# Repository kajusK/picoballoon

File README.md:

Picoballoon challange 2019, team deadbadger probe
-------------------------------------------------

This repo contains source codes and hw design of the picoballoon probe designed
for https://www.hvezdarna.cz/?p=7694.

Due to the lack of free time, the pcb is very suboptimal as I needed single sided
board with wider traces for diy manufacturing process (made it few days before the
launch, didn't have enough time to send it to a pcb house).

The circuit contains:
- MCU stm32f070
- GPS u-blox max-m8
- Lora module HPD13
- Analog thermometer
- Digital pressure sensor MS5607 (failed to make it working before start - getting nack all the time)
- Solar panel that charges the supercap (wanted bare cells from china, but delivery time was too long, used one quite heavy panel from my junk box)
- 3.3 V boost switching power supply with startup circuit (starts around 2,5 V)

The software is quite simplified too. The Lmic library takes care of the LoRa
communications. Minmea handles processing nmea messages from gps. For future
reference, the libopencm3 is not the best option when dealing with stm32f0
family, I've had serious issues with rtc wakeup timer and failed
to wake up from deep sleep on rtc events anyway...

The code does following:
- Initialize peripherals
- Send LoRa join request
- Try to get the gps position
- After gps fix or timeout, send data over the LoRa connection and shutdown

Sending period depends on amount of sunlight (solar cell current) and supercap
capacity.

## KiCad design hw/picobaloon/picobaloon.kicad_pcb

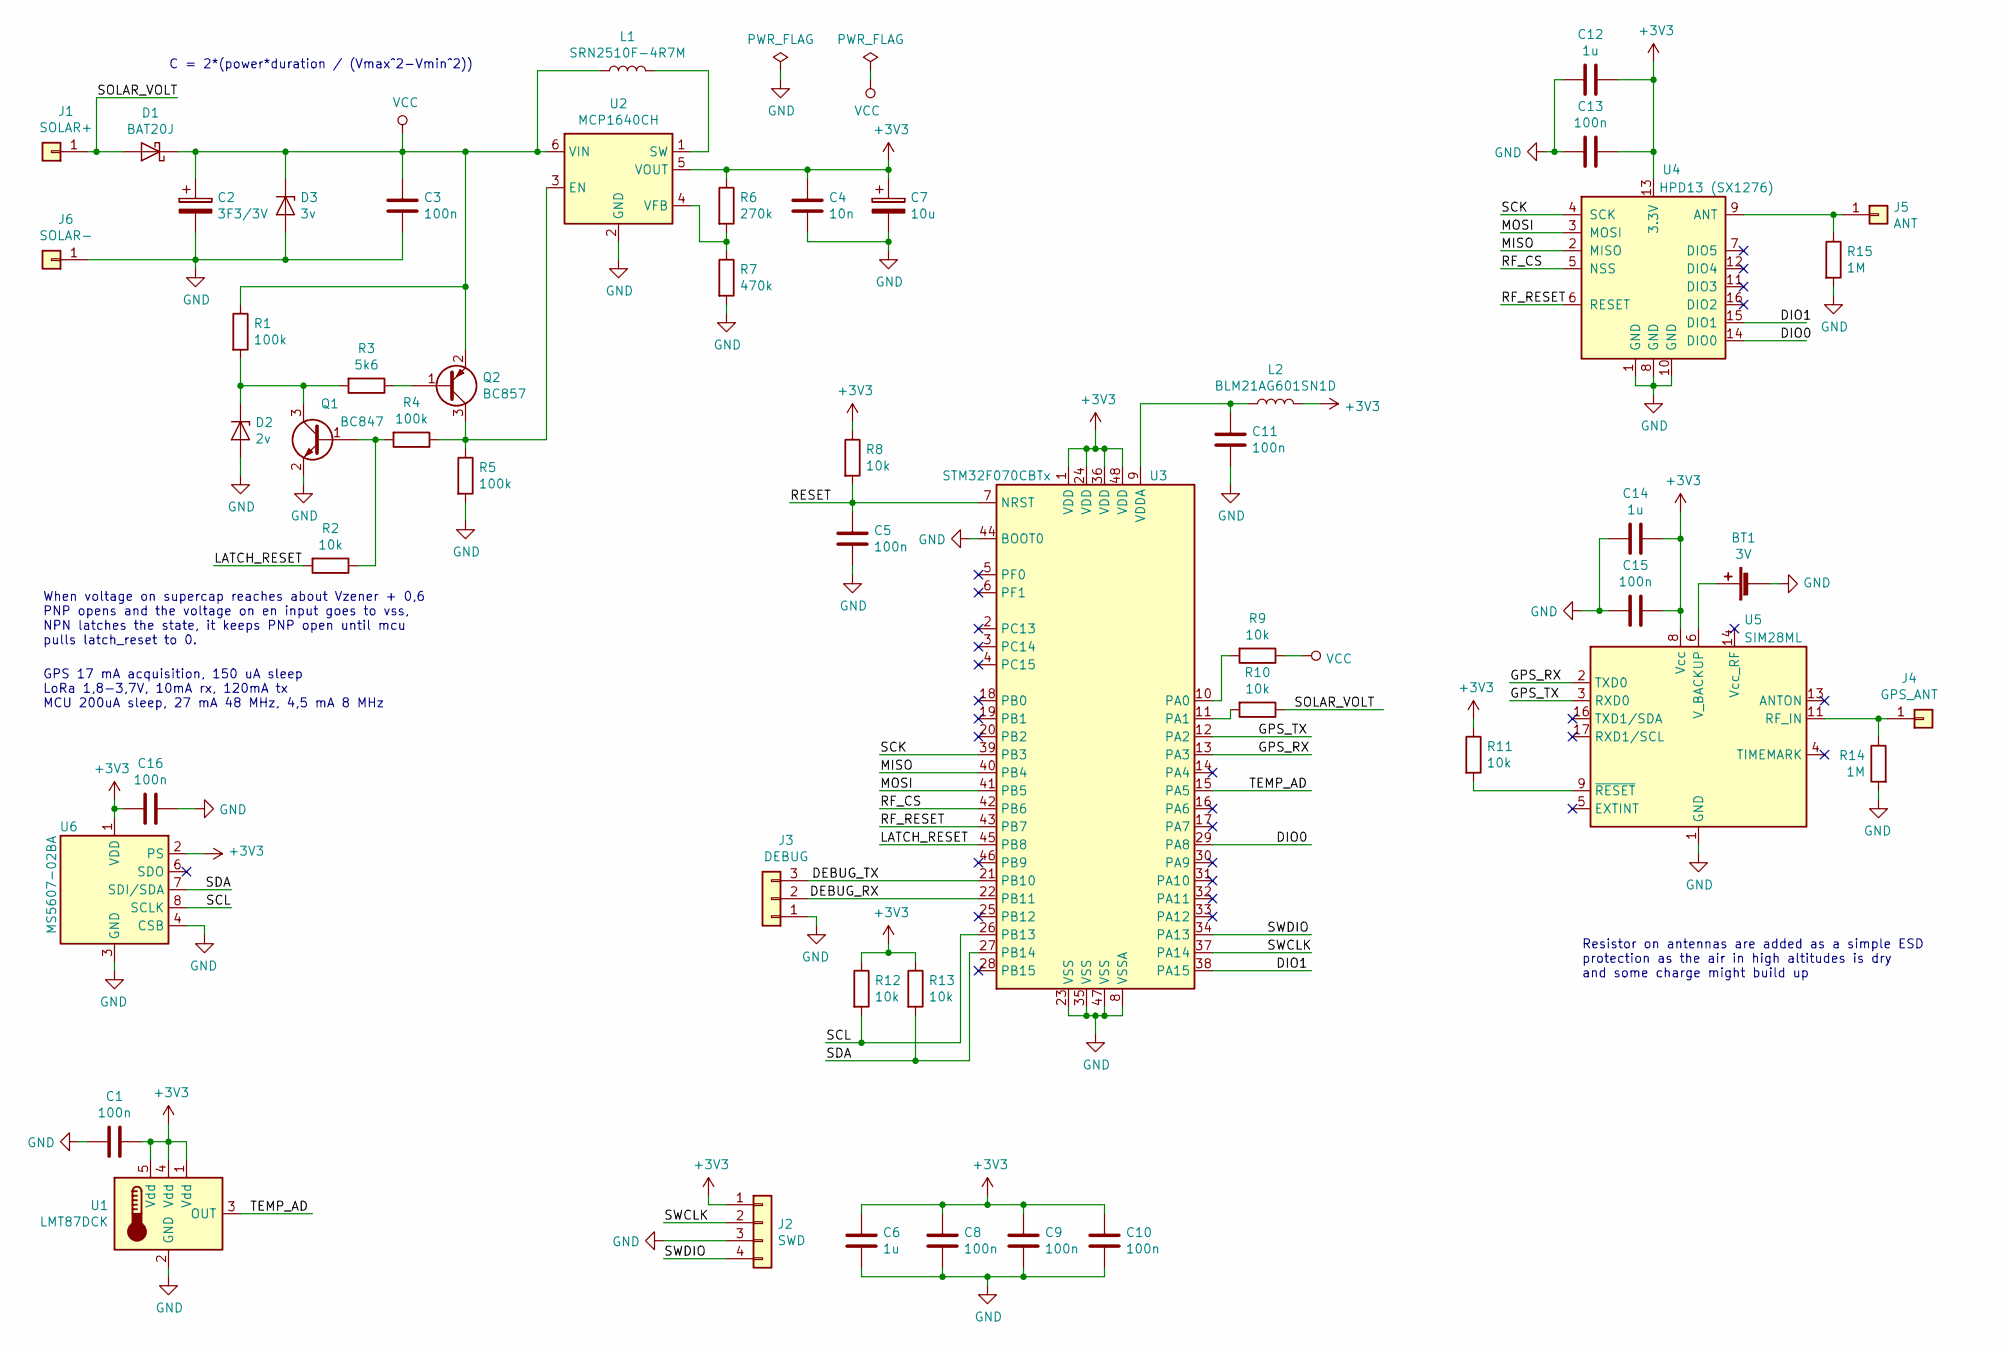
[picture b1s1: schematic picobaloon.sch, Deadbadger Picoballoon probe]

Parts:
BT1: 3V; BatteryHolder_Keystone_3001_1x12mm
C1, C3, C5, C8, C9, C10, C11, C13, C15, C16: 100n; C_0805_2012Metric
C2: 3F3/3V; CP_Radial_D8.0mm_P3.50mm
C4: 10n; C_0805_2012Metric
C6, C12, C14: 1u; C_0805_2012Metric
C7: 10u; C_0805_2012Metric
D1: BAT20J; D_SOD-323
D2: 2v; D_SOD-323
D3: 3v; D_SOD-323
J1: SOLAR+; SolderWirePad_1x01_Drill1.2mm
J2: SWD; PinHeader_1x04_P2.54mm_Vertical
J3: DEBUG; PinHeader_1x03_P2.54mm_Vertical
J4: GPS_ANT; SolderWirePad_1x01_Drill1.2mm
J5: ANT; SolderWirePad_1x01_Drill1.2mm
J6: SOLAR-; SolderWirePad_1x01_Drill1.2mm
L1: SRN2510F-4R7M; L_Abracon_ASPI-3012S
L2: BLM21AG601SN1D; L_0805_2012Metric
Q1: BC847; SOT-23
Q2: BC857; SOT-23
R1, R4, R5: 100k; R_0805_2012Metric
R2, R8, R9, R10, R11, R12, R13: 10k; R_0805_2012Metric
R3: 5k6; R_0805_2012Metric
R6: 270k; R_0805_2012Metric
R7: 470k; R_0805_2012Metric
R14, R15: 1M; R_0805_2012Metric
U1: LMT87DCK; SOT-353_SC-70-5
U2: MCP1640CH; SOT-23-6
U3: STM32F070CBTx; LQFP-48_7x7mm_P0.5mm
U4: HPD13 (SX1276); HOPERF_RFM9XW_SMD
U5: SIM28ML
U6: MS5607-02BA; LGA-8_3x5mm_P1.25mm

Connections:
+3V3: C1.1, C4.1, C6.1, C7.1, C8.1, C9.1, C10.1, C12.1, C13.1, C14.1, C15.1, C16.1, J2.1, L2.2, R6.1, R8.1, R11.1, R12.1, R13.1, U1.1 (Vdd), U1.4 (Vdd), U1.5 (Vdd), U2.5 (VOUT), U3.1 (VDD), U3.24 (VDD), U3.36 (VDD), U3.48 (VDD), U4.13 (3.3V), U5.8 (Vcc), U6.1 (VDD), U6.2 (PS)
/DEBUG_RX: J3.2, U3.22 (PB11)
/DEBUG_TX: J3.3, U3.21 (PB10)
/DIO0: U3.29 (PA8), U4.14 (DIO0)
/DIO1: U3.38 (PA15), U4.15 (DIO1)
/GPS_RX: U3.13 (PA3), U5.2 (TXD0)
/GPS_TX: U3.12 (PA2), U5.3 (RXD0)
/LATCH_RESET: R2.2, U3.45 (PB8)
/MISO: U3.40 (PB4), U4.2 (MISO)
/MOSI: U3.41 (PB5), U4.3 (MOSI)
/RESET: C5.1, R8.2, U3.7 (NRST)
/RF_CS: U3.42 (PB6), U4.5 (NSS)
/RF_RESET: U3.43 (PB7), U4.6 (RESET)
/SCK: U3.39 (PB3), U4.4 (SCK)
/SCL: R12.2, U3.26 (PB13), U6.8 (SCLK)
/SDA: R13.2, U3.27 (PB14), U6.7 (SDI/SDA)
/SOLAR_VOLT: D1.2 (A), J1.1, R10.1
/SWCLK: J2.2, U3.37 (PA14)
/SWDIO: J2.4, U3.34 (PA13)
/TEMP_AD: U1.3 (OUT), U3.15 (PA5)
GND: BT1.2 (-), C1.2, C2.2, C3.2, C4.2, C5.2, C6.2, C7.2, C8.2, C9.2, C10.2, C11.2, C12.2, C13.2, C14.2, C15.2, C16.2, D2.2 (A), D3.2 (A), J2.3, J3.1, J6.1, Q1.2 (E), R5.2, R7.2, R14.2, R15.2, U1.2 (GND), U2.2 (GND), U3.8 (VSSA), U3.23 (VSS), U3.35 (VSS), U3.44 (BOOT0), U3.47 (VSS), U4.1 (GND), U4.8 (GND), U4.10 (GND), U5.1 (GND), U5.10 (GND), U5.12 (GND), U6.3 (GND), U6.4 (CSB), U6.5 (CSB)
unnamed: BT1.1 (+), U5.6 (V_BACKUP)
unnamed: C11.1, L2.1, U3.9 (VDDA)
unnamed: D2.1 (K), Q1.3 (C), R1.2, R3.2
unnamed: J4.1, R14.1, U5.11 (RF_IN)
unnamed: J5.1, R15.1, U4.9 (ANT)
unnamed: L1.2, U2.1 (SW)
unnamed: Q1.1 (B), R2.1, R4.2
unnamed: Q2.1 (B), R3.1
unnamed: Q2.3 (C), R4.1, R5.1, U2.3 (EN)
unnamed: R6.2, R7.1, U2.4 (VFB)
unnamed: R9.2, U3.10 (PA0)
unnamed: R10.2, U3.11 (PA1)
unnamed: R11.2, U5.9 (~RESET)
VCC: C2.1, C3.1, D1.1 (K), D3.1 (K), L1.1, Q2.2 (E), R1.1, R9.1, U2.6 (VIN)

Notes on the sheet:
C = 2*(power*duration / (Vmax^2-Vmin^2))
GPS 17 mA acquisition, 150 uA sleep LoRa 1,8-3,7V, 10mA rx, 120mA tx MCU 200uA sleep, 27 mA 48 MHz, 4,5 mA 8 MHz
When voltage on supercap reaches about Vzener + 0,6 PNP opens and the voltage on en input goes to vss, NPN latches the state, it keeps PNP open until mcu pulls latch_reset to 0.
Resistor on antennas are added as a simple ESD protection as the air in high altitudes is dry and some charge might build up

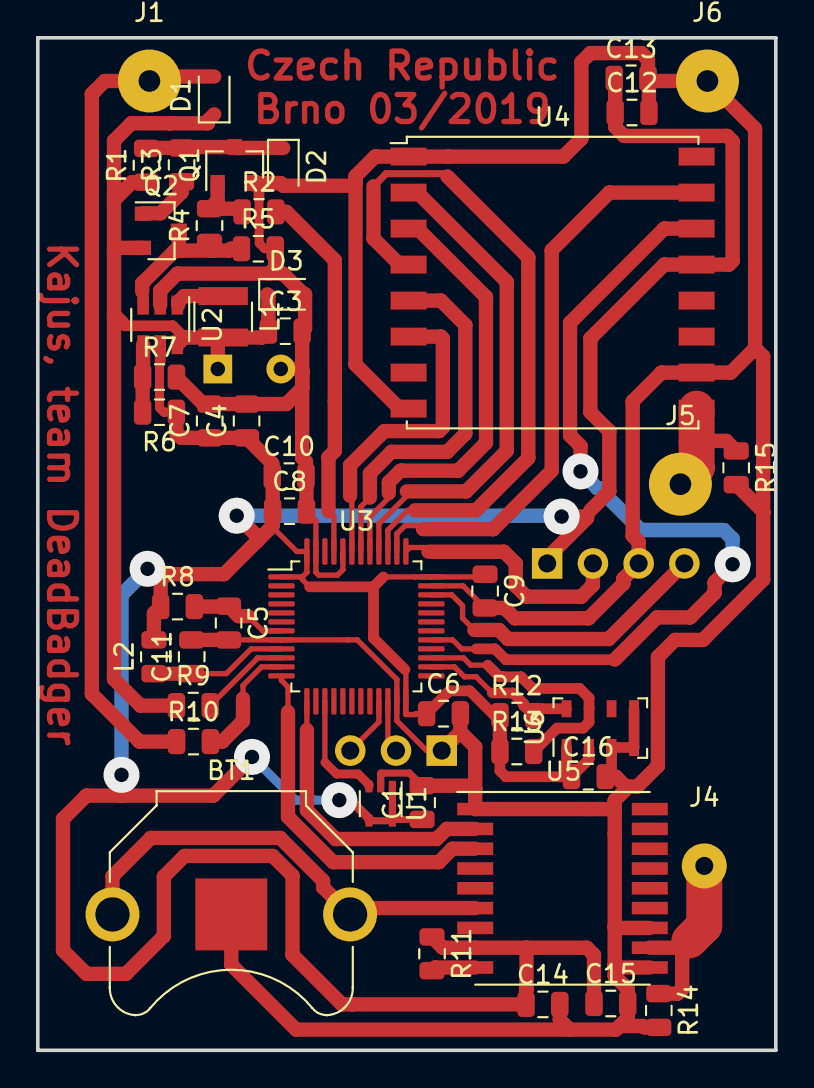
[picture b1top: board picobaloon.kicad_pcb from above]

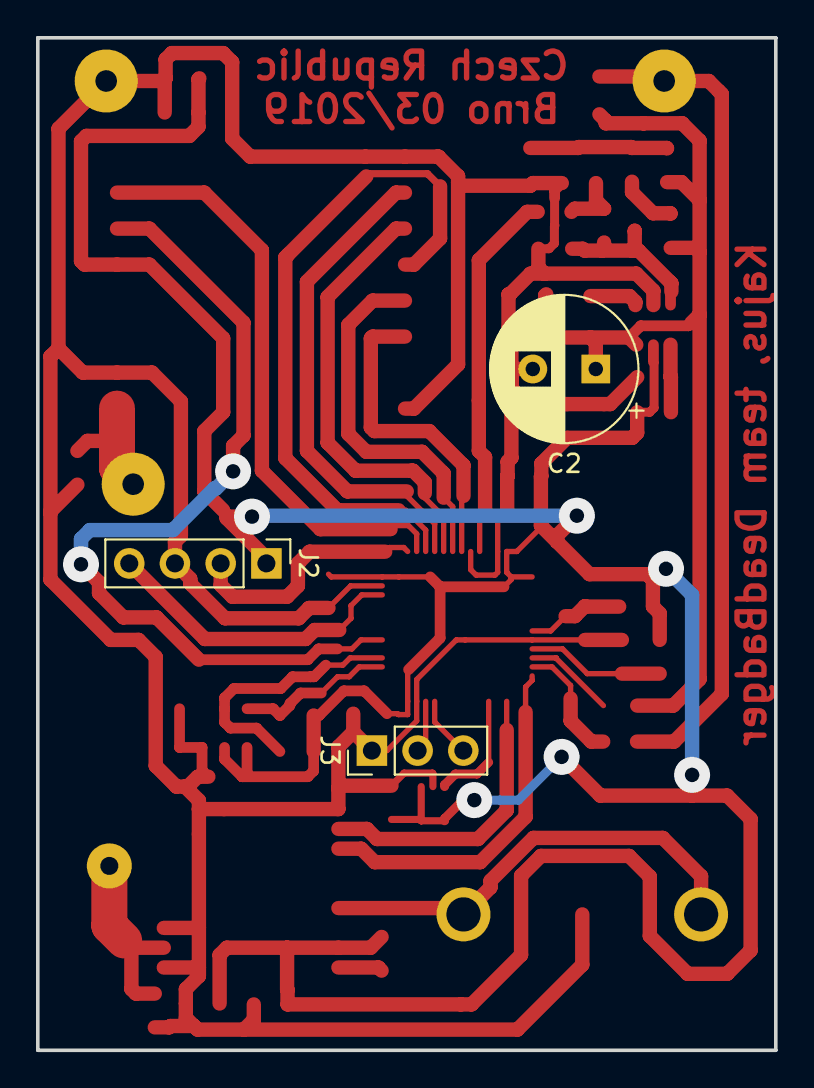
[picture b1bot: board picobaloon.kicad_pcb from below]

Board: 2 copper layers, 41.0 x 56.3 mm, 51 parts (3 on the bottom side), 35 nets.

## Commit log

2019-02-06 Added lmic and libopencm3 libs
2019-02-06 Hw revision v0.1
2019-02-06 HW revision 2 - added pressure sensor
2019-02-06 HW revision 3. Added resistors for simple esd protection
2019-02-17 Updated schematic to match the final symbol in the official repo
2019-02-17 Initial sw commit
2019-02-17 Moved few files to drivers
2019-02-17 Added gitignore
2019-02-17 Updated gps processing function name
2019-02-17 Added sensors measurements
2019-02-17 Fixed lora names and include
2019-02-17 Added configuration command for ublox gps
2019-02-17 Increased wdg timeout
2019-02-17 Added basics of probe logic
2019-02-17 Make lora structure packed
2019-02-17 Added power control to gps driver
2019-02-19 Enabled adc clock
2019-02-19 Fixed uart output clock
2019-02-19 Added forgotten watchdog start
2019-02-19 Used modified i2c transmit function from library, original gets to infinite loop on nack
2019-02-19 Fixed gps driver transmit data
2019-02-20 Fixed lmic hal (there was a bug in spi library)
2019-02-20 Removed unused file
2019-02-22 Fixed lmic driver (timing, interrupts,...)
2019-02-22 Fixed lora printouts, added lmic error setup to init
2019-02-22 Added nmea decoding library
2019-02-22 Enable vint reference
2019-02-22 Fixed bug in exti reading
2019-02-22 Removed print on gps
2019-02-24 Added clearing of the gps fix
2019-02-24 Start joining immediately after lora startup
2019-02-24 Moved probe logic to it's own file
2019-02-24 Fixed mcu type and enable printf for floats
2019-03-03 Added support for sleep, waking up doesnt work yet for some reason...
2019-03-03 Reset pressure sensor before initializing
2019-03-03 Updated critical voltage level for sending data
2019-03-03 Increased possible timing error for receive windows
2019-03-03 custom config
2019-03-03 Last changes
2019-03-03 Added readme
2019-03-04 Added some powersaving before sending lora
